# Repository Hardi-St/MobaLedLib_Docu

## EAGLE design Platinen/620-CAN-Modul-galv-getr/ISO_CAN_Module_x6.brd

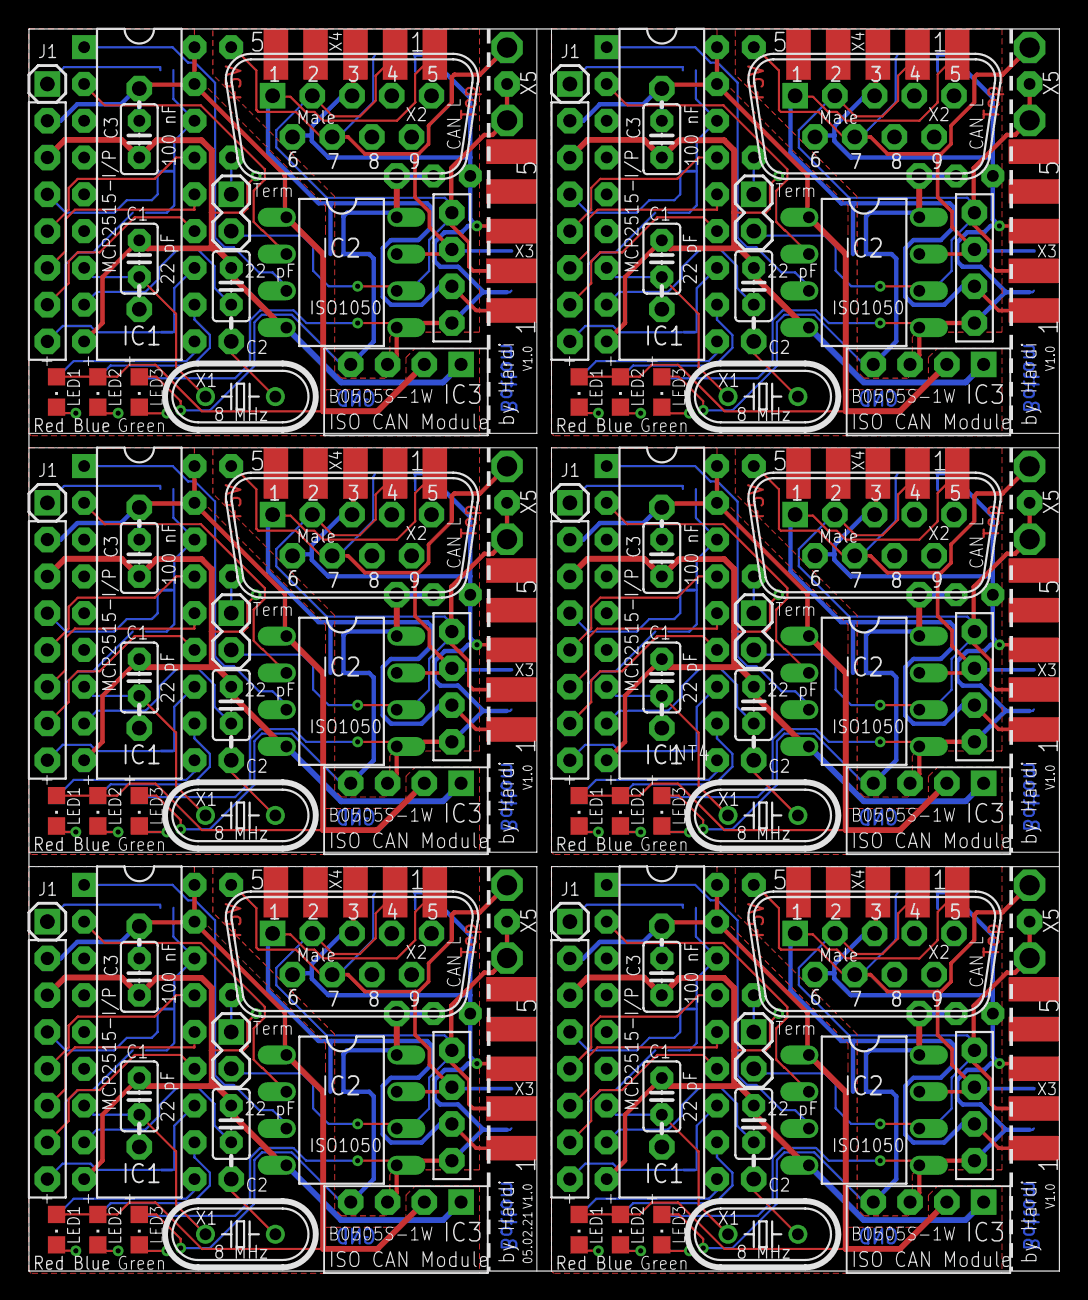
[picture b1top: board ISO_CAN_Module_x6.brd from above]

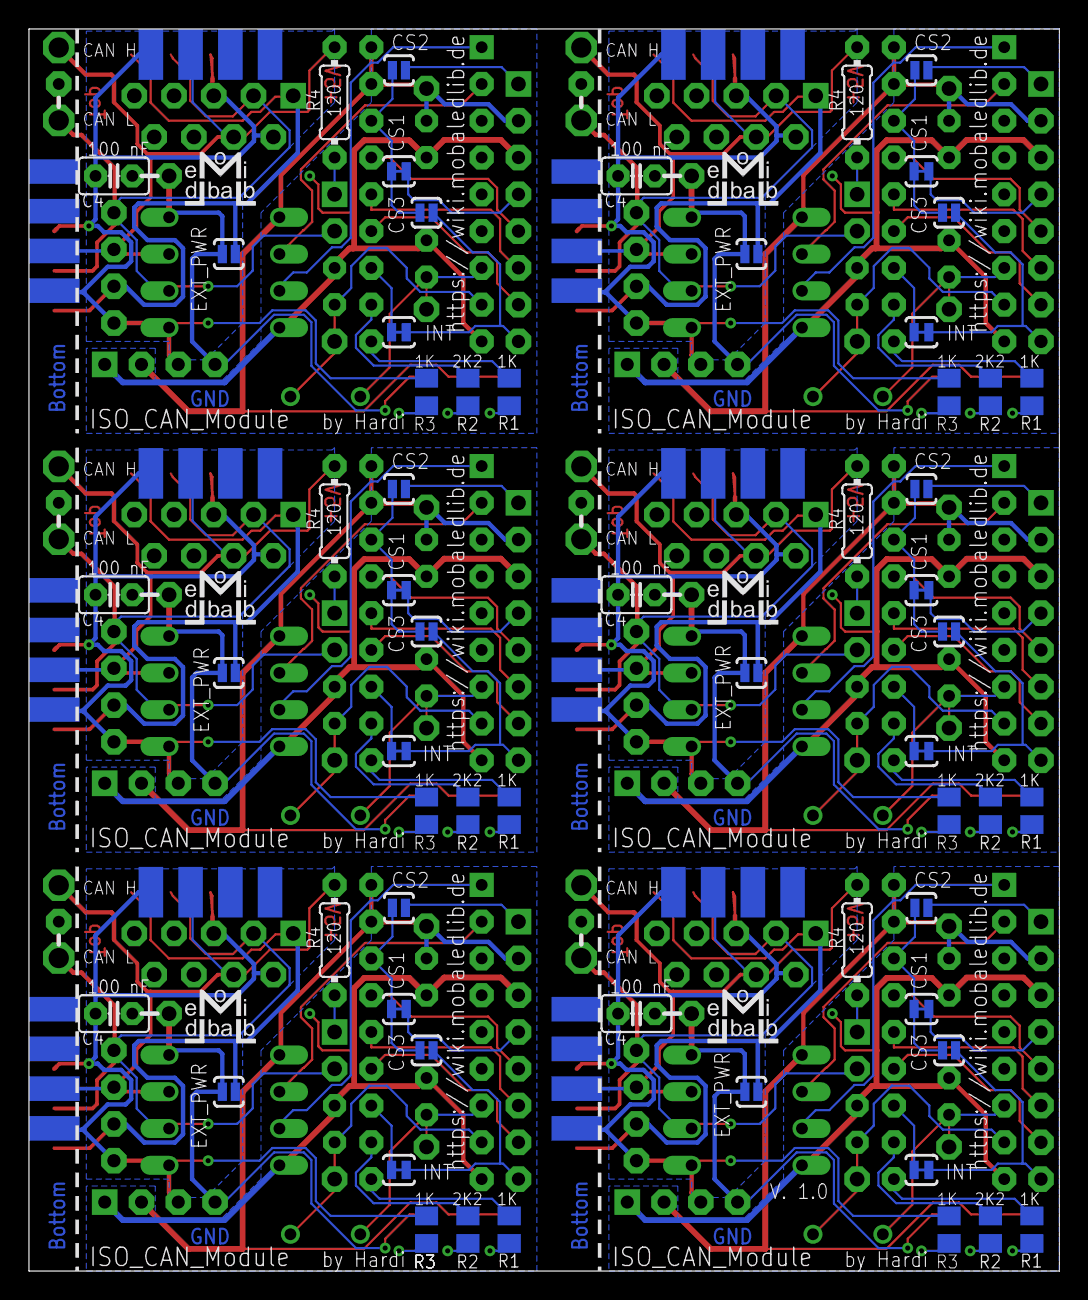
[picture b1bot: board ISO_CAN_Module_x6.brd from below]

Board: 2 copper layers, 71.2 x 85.8 mm, 186 parts (60 on the bottom side), 150 nets.

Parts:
C1, C2, C5, C6, C9, C10, C13, C14, C17, C18, C21, C22: 22 pF; C2.5-2
C3, C4, C7, C8, C11, C12, C15, C16, C19, C20, C23, C24: 100 nF; C2.5-2
CAN1, CAN2, CAN3, CAN4, CAN5, CAN6: MCP2515_ISO_CAN_PINS; MCP2515_ISO_CAN
CON1, CON2, CON3, CON4, CON5, CON8: Term; 1X02
CS1, CS5, CS8, CS11, CS14, CS17: SOLDERJUMPERTRACE; SJ_2S-TRACE
CS2, CS3, CS4, CS6, CS7, CS9, CS10, CS12, CS13, CS15, CS16, CS18: SOLDERJUMPERNO; SJ_2S-NO
EXT_PWR, EXT_PWR1, EXT_PWR2, EXT_PWR3, EXT_PWR4, EXT_PWR5: SOLDERJUMPERNO; SJ_2S-NO
IC1, IC5, IC8, IC11, IC14, IC17: MCP2515-I/P; DIL18
IC2, IC4, IC7, IC10, IC13, IC16: ISO1050; DIL08
IC3, IC6, IC9, IC12, IC15, IC18: B0505S-1W; DCDC-TEA_NME
INT, INT1, INT2, INT3, INT4, INT5: SOLDERJUMPERTRACE; SJ_2S-TRACE
J1, J6, J11, J16, J21, J26: 1X01
J2, J3, J4, J5, J7, J8, J9, J10, J12, J13, J14, J15, J17, J18, J19, J20, J22, J23, J24, J25, J27, J28, J29, J30: 1X01S
LED1, LED5, LED8, LED11, LED14, LED17: Red; CHIPLED_0805
LED2, LED4, LED7, LED10, LED13, LED16: Blue; CHIPLED_0805
LED3, LED6, LED9, LED12, LED15, LED18: Green; CHIPLED_0805
R1, R3, R6, R8, R10, R12, R14, R16, R18, R20, R22, R24: 1K; M0805
R2, R5, R9, R13, R17, R21: 2K2; M0805
R4, R7, R11, R15, R19, R23: 120; 0204/7
X1, X6, X11, X16, X21, X26: 8 MHz; HC49U-V
X2, X8, X13, X18, X23, X28: Male; M09VB
X3, X4, X7, X9, X12, X14, X17, X19, X22, X24, X27, X29: Male; M09D
X5, X10, X15, X20, X25, X30: AK500/2+M

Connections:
+5V: C3.1, CAN1.1, IC1.17, IC1.18, IC2.1, IC3.V_IN, J4.1, LED1.A, LED2.A
+5V1: C7.1, CAN2.1, IC4.1, IC5.17, IC5.18, IC6.V_IN, J9.1, LED4.A, LED5.A
+5V2: C11.1, CAN3.1, IC7.1, IC8.17, IC8.18, IC9.V_IN, J14.1, LED7.A, LED8.A
+5V3: C15.1, CAN4.1, IC10.1, IC11.17, IC11.18, IC12.V_IN, J19.1, LED10.A, LED11.A
+5V4: C19.1, CAN5.1, IC13.1, IC14.17, IC14.18, IC15.V_IN, J24.1, LED13.A, LED14.A
+5V5: C23.1, CAN6.1, IC16.1, IC17.17, IC17.18, IC18.V_IN, J29.1, LED16.A, LED17.A
CAN_H: CAN1.9, IC2.7, R4.2, X2.7, X3.7, X4.7, X5.2
CAN_H1: CAN2.9, IC4.7, R7.2, X7.7, X8.7, X9.7, X10.2
CAN_H2: CAN3.9, IC7.7, R11.2, X12.7, X13.7, X14.7, X15.2
CAN_H3: CAN4.9, IC10.7, R15.2, X17.7, X18.7, X19.7, X20.2
CAN_H4: CAN5.9, IC13.7, R19.2, X22.7, X23.7, X24.7, X25.2
CAN_H5: CAN6.9, IC16.7, R23.2, X27.7, X28.7, X29.7, X30.2
CAN_L: CAN1.8, CON8.2, IC2.6, X2.2, X3.2, X4.2, X5.1, X5.M
CAN_L1: CAN2.8, CON1.2, IC4.6, X7.2, X8.2, X9.2, X10.1, X10.M
CAN_L2: CAN3.8, CON2.2, IC7.6, X12.2, X13.2, X14.2, X15.1, X15.M
CAN_L3: CAN4.8, CON3.2, IC10.6, X17.2, X18.2, X19.2, X20.1, X20.M
CAN_L4: CAN5.8, CON4.2, IC13.6, X22.2, X23.2, X24.2, X25.1, X25.M
CAN_L5: CAN6.8, CON5.2, IC16.6, X27.2, X28.2, X29.2, X30.1, X30.M
CS: CS1.2, CS2.2, CS3.2, IC1.16
CS1: CS4.2, CS5.2, CS6.2, IC5.16
CS2: CS7.2, CS8.2, CS9.2, IC8.16
CS3: CS10.2, CS11.2, CS12.2, IC11.16
CS4: CS13.2, CS14.2, CS15.2, IC14.16
CS5: CS16.2, CS17.2, CS18.2, IC17.16
CS_CAN0: CAN1.3, CS1.1
CS_CAN1: CAN2.3, CS5.1
CS_CAN2: CAN3.3, CS8.1
CS_CAN3: CAN4.3, CS11.1
CS_CAN4: CAN5.3, CS14.1
CS_CAN5: CAN6.3, CS17.1
CS_INT: CAN1.7, CS3.1, INT.1
CS_INT1: CAN2.7, CS6.1, INT1.1
CS_INT2: CAN3.7, CS9.1, INT2.1
CS_INT3: CAN4.7, CS12.1, INT3.1
CS_INT4: CAN5.7, CS15.1, INT4.1
CS_INT5: CAN6.7, CS18.1, INT5.1
CS_J1: CS2.1, J1.1
CS_J2: CS4.1, J6.1
CS_J3: CS7.1, J11.1
CS_J4: CS10.1, J16.1
CS_J5: CS13.1, J21.1
CS_J6: CS16.1, J26.1
GND: C1.2, C2.2, C3.2, CAN1.2, IC1.9, IC2.4, IC3.G_IN
GND1: C5.2, C6.2, C7.2, CAN2.2, IC4.4, IC5.9, IC6.G_IN
GND2: C4.1, CAN1.11, IC2.5, IC3.G_OUT, R3.1, X2.3, X2.6, X3.3, X3.6, X4.3, X4.6
GND3: C8.1, CAN2.11, IC4.5, IC6.G_OUT, R8.1, X7.3, X7.6, X8.3, X8.6, X9.3, X9.6
GND4: C9.2, C10.2, C11.2, CAN3.2, IC7.4, IC8.9, IC9.G_IN
GND5: C12.1, CAN3.11, IC7.5, IC9.G_OUT, R12.1, X12.3, X12.6, X13.3, X13.6, X14.3, X14.6
GND6: C13.2, C14.2, C15.2, CAN4.2, IC10.4, IC11.9, IC12.G_IN
GND7: C16.1, CAN4.11, IC10.5, IC12.G_OUT, R16.1, X17.3, X17.6, X18.3, X18.6, X19.3, X19.6
GND8: C17.2, C18.2, C19.2, CAN5.2, IC13.4, IC14.9, IC15.G_IN
GND9: C20.1, CAN5.11, IC13.5, IC15.G_OUT, R20.1, X22.3, X22.6, X23.3, X23.6, X24.3, X24.6
GND10: C21.2, C22.2, C23.2, CAN6.2, IC16.4, IC17.9, IC18.G_IN
GND11: C24.1, CAN6.11, IC16.5, IC18.G_OUT, R24.1, X27.3, X27.6, X28.3, X28.6, X29.3, X29.6
INT0: IC1.12, INT.2
INT1: IC5.12, INT1.2
INT2: IC8.12, INT2.2
INT3: IC11.12, INT3.2
INT4: IC14.12, INT4.2
INT5: IC17.12, INT5.2
LED1: LED1.C, R1.1
LED2: LED2.C, R2.1
LED3: LED3.C, R3.2
LED4: LED4.C, R5.1
LED5: LED5.C, R6.1
LED6: LED6.C, R8.2
LED7: LED7.C, R9.1
LED8: LED8.C, R10.1
LED9: LED9.C, R12.2
LED10: LED10.C, R13.1
LED11: LED11.C, R14.1
LED12: LED12.C, R16.2
LED13: LED13.C, R17.1
LED14: LED14.C, R18.1
LED15: LED15.C, R20.2
LED16: LED16.C, R21.1
LED17: LED17.C, R22.1
LED18: LED18.C, R24.2
unnamed: IC5.11, R5.2
unnamed: IC5.10, R6.2
unnamed: IC8.11, R9.2
unnamed: IC8.10, R10.2
unnamed: IC11.11, R13.2
unnamed: IC11.10, R14.2
unnamed: IC14.11, R17.2
unnamed: IC14.10, R18.2
unnamed: IC1.11, R2.2
unnamed: IC17.11, R21.2
unnamed: IC17.10, R22.2
unnamed: IC1.10, R1.2
OSC1: C2.1, IC1.8, J3.1, X1.2
OSC2: C1.1, IC1.7, J2.1, X1.1
OSC3: C5.1, IC5.7, J7.1, X6.1
OSC4: C6.1, IC5.8, J8.1, X6.2
OSC5: C9.1, IC8.7, J12.1, X11.1
OSC6: C10.1, IC8.8, J13.1, X11.2
OSC7: C13.1, IC11.7, J17.1, X16.1
OSC8: C14.1, IC11.8, J18.1, X16.2
OSC9: C17.1, IC14.7, J22.1, X21.1
OSC10: C18.1, IC14.8, J23.1, X21.2
OSC11: C21.1, IC17.7, J27.1, X26.1
OSC12: C22.1, IC17.8, J28.1, X26.2
RXCAN: IC1.2, IC2.2
RXCAN1: IC4.2, IC5.2
RXCAN2: IC7.2, IC8.2
RXCAN3: IC10.2, IC11.2
RXCAN4: IC13.2, IC14.2
RXCAN5: IC16.2, IC17.2
SCK: CAN1.6, IC1.13
SCK1: CAN2.6, IC5.13
SCK2: CAN3.6, IC8.13
SCK3: CAN4.6, IC11.13
SCK4: CAN5.6, IC14.13
SCK5: CAN6.6, IC17.13
SI: CAN1.5, IC1.14
SI1: CAN2.5, IC5.14
SI2: CAN3.5, IC8.14
SI3: CAN4.5, IC11.14
SI4: CAN5.5, IC14.14
SI5: CAN6.5, IC17.14
SO: CAN1.4, IC1.15
SO1: CAN2.4, IC5.15
SO2: CAN3.4, IC8.15
SO3: CAN4.4, IC11.15
SO4: CAN5.4, IC14.15
SO5: CAN6.4, IC17.15
TERM: CON8.1, R4.1
TERM1: CON1.1, R7.1
TERM2: CON2.1, R11.1
TERM3: CON3.1, R15.1
TERM4: CON4.1, R19.1
TERM5: CON5.1, R23.1
TXCAN: IC1.1, IC2.3
TXCAN1: IC4.3, IC5.1
TXCAN2: IC7.3, IC8.1
TXCAN3: IC10.3, IC11.1
TXCAN4: IC13.3, IC14.1
TXCAN5: IC16.3, IC17.1
VCC1: C8.2, EXT_PWR1.1, IC4.8, IC6.V_OUT, J10.1, LED6.A
VCC2: C4.2, EXT_PWR.1, IC2.8, IC3.V_OUT, J5.1, LED3.A
VCC2_EXT: CAN1.10, EXT_PWR.2, X2.1, X3.1, X4.1
VCC2_EXT1: CAN2.10, EXT_PWR1.2, X7.1, X8.1, X9.1
VCC2_EXT2: CAN3.10, EXT_PWR2.2, X12.1, X13.1, X14.1
VCC2_EXT3: CAN4.10, EXT_PWR3.2, X17.1, X18.1, X19.1
VCC2_EXT4: CAN5.10, EXT_PWR4.2, X22.1, X23.1, X24.1
VCC2_EXT5: CAN6.10, EXT_PWR5.2, X27.1, X28.1, X29.1
VCC3: C12.2, EXT_PWR2.1, IC7.8, IC9.V_OUT, J15.1, LED9.A
VCC4: C16.2, EXT_PWR3.1, IC10.8, IC12.V_OUT, J20.1, LED12.A
VCC5: C20.2, EXT_PWR4.1, IC13.8, IC15.V_OUT, J25.1, LED15.A
VCC6: C24.2, EXT_PWR5.1, IC16.8, IC18.V_OUT, J30.1, LED18.A

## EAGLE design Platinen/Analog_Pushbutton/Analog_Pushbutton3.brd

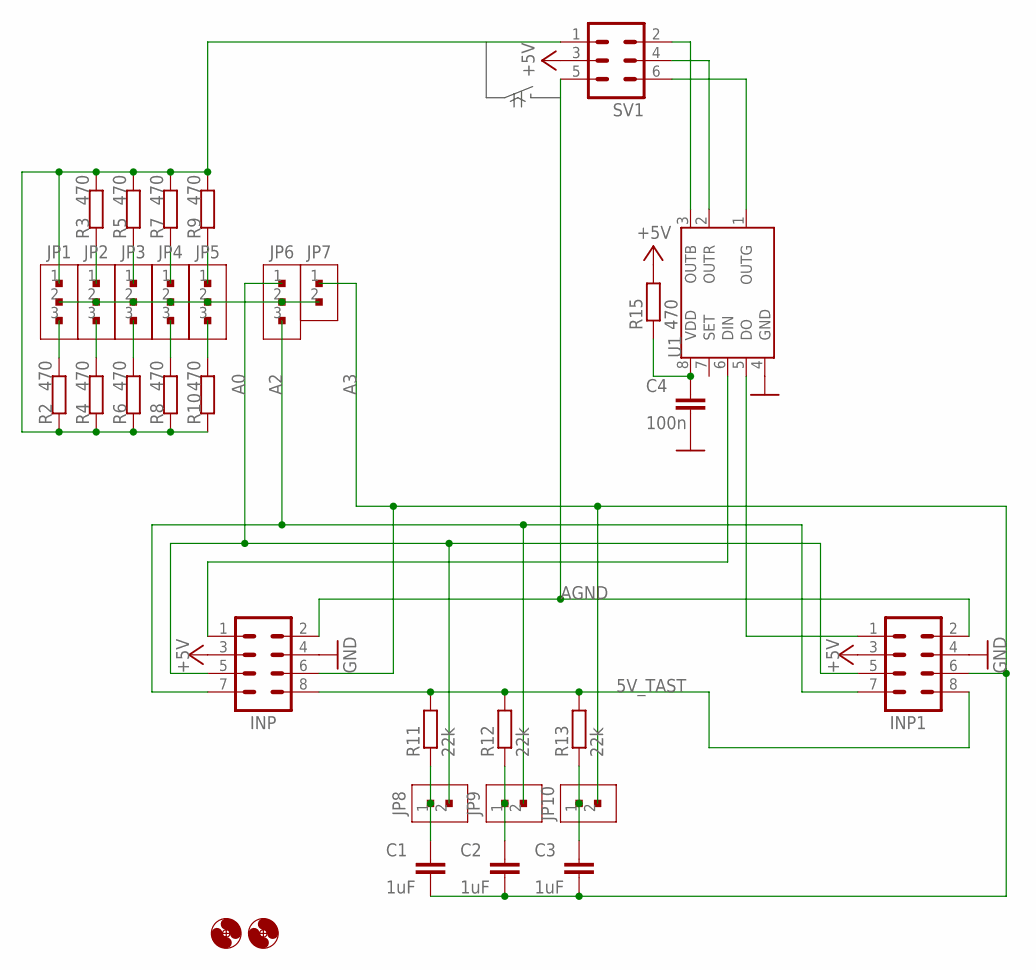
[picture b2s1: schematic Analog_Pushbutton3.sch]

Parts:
C1, C2, C3: 1uF; C0603
C4: 100n; C0603
H1, H2: MOUNT-HOLE3.0; 3,0
INP, INP1: CON-HARTING-ML_ML08
JP1, JP2, JP3, JP4, JP5, JP6: PINHD-1X3CB; 1X03-CLEANBIG
JP7, JP8, JP9, JP10: PINHD-1X2; 1X02
R2, R3, R4, R5, R6, R7, R8, R9, R10, R15: 470; R0603
R11, R12, R13: 22k; R0603
SV1: CON-HARTING-ML_ML6
U1: S3PO_MODUL_WS2811_SOUND_MP3-TF-16P_WS2811_AND_ATT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; SOP8

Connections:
5V_TAST: INP.8, INP1.8, R11.2, R12.2, R13.2
+5V: INP.3, INP1.3, R15.2, SV1.3
A0: INP.5, INP1.5, JP6.1, JP8.2
A2: INP.7, INP1.7, JP6.3, JP9.2
A3: C1.2, C2.2, C3.2, INP.6, INP1.6, JP7.1, JP10.2
AGND: INP.2, INP1.2, SV1.5
GND: C4.2, INP.4, INP1.4, U1.4 (GND)
unnamed: SV1.4, U1.2 (OUTR)
unnamed: SV1.6, U1.1 (OUTG)
unnamed: SV1.2, U1.3 (OUTB)
unnamed: INP.1, U1.6 (DIN)
unnamed: INP1.1, U1.5 (DO)
unnamed: C1.1, JP8.1, R11.1
unnamed: JP1.3, R2.2
unnamed: JP1.1, R2.1, R3.2, R4.1, R5.2, R6.1, R7.2, R8.1, R9.2, R10.1, SV1.1
unnamed: JP2.3, R4.2
unnamed: JP2.1, R3.1
unnamed: JP3.3, R6.2
unnamed: JP3.1, R5.1
unnamed: JP4.3, R8.2
unnamed: JP4.1, R7.1
unnamed: JP5.3, R10.2
unnamed: JP5.1, R9.1
unnamed: C2.1, JP9.1, R12.1
unnamed: C3.1, JP10.1, R13.1
unnamed: JP1.2, JP2.2, JP3.2, JP4.2, JP5.2, JP6.2, JP7.2
unnamed: C4.1, R15.1, U1.8 (VDD)

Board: 2 copper layers, 33 parts (0 on the bottom side), 27 nets, no tracks yet.

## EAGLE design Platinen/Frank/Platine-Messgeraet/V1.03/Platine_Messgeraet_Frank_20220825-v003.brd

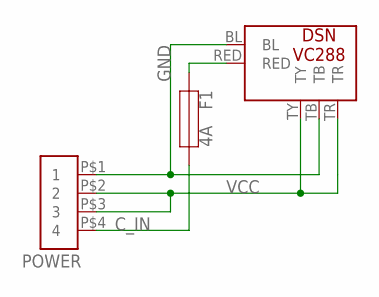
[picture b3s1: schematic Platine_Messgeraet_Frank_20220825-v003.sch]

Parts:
F1: 4A; FUSE_5X20-L
POWER: CB-SCREW-4P0°; CTB932VD-4
U$1: DSN-VC288

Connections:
C_IN: F1.1, POWER.P$4 (4)
GND: POWER.P$1 (1), U$1.BL, U$1.TB
unnamed: F1.2, U$1.RED
VCC: POWER.P$2 (2), POWER.P$3 (3), U$1.TR, U$1.TY

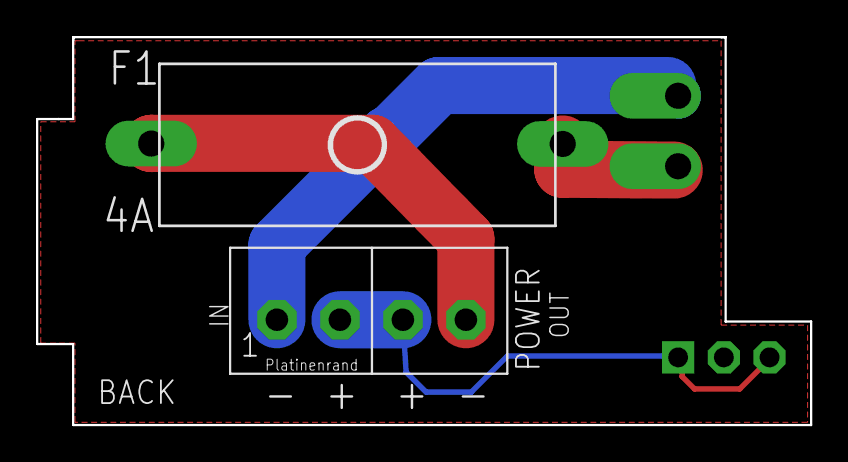
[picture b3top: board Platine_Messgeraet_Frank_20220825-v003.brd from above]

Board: 2 copper layers, 43.0 x 21.6 mm, 3 parts (0 on the bottom side), 4 nets.

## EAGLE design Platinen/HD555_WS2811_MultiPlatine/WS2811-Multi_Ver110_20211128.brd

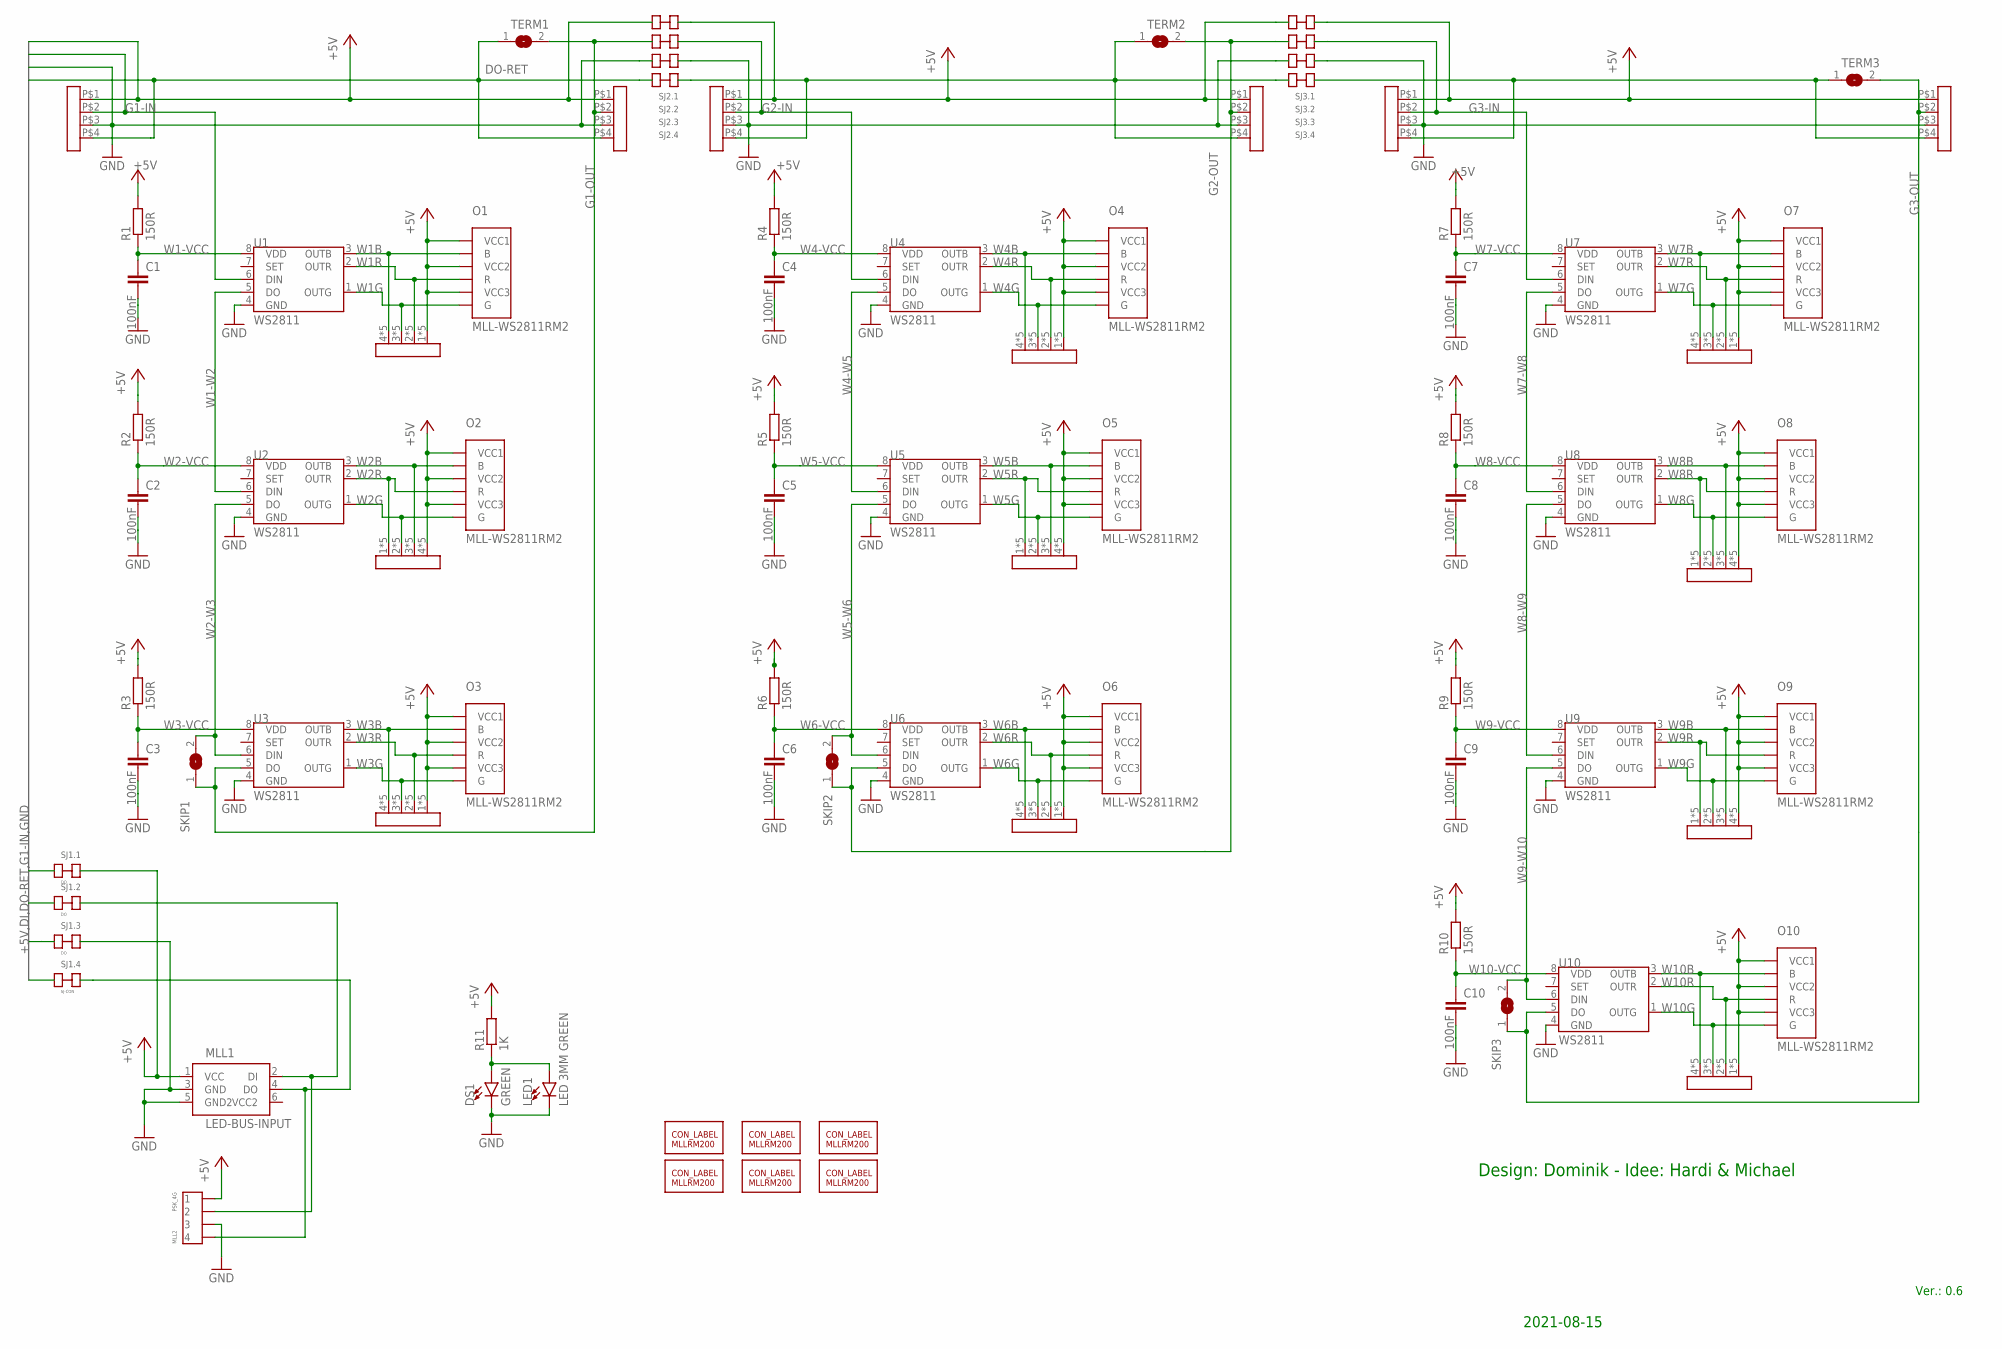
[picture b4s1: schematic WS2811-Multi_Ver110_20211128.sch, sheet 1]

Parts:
C1, C2, C3, C4, C5, C6, C7, C8, C9, C10: 100nF; C1206
DS1: GREEN; LED-1206
LED1: LED 3MM GREEN; LED_3MM
M1_IN, M1_OUT, M2_IN, M2_OUT, M3_IN, M3_OUT: 4XRM254
MLL1: LED-BUS-INPUT; IDC6
MLL2: PSK_4G; PSSG4
O1, O2, O3, O4, O5, O6, O7, O8, O9, O10: MLL-WS2811RM2; MLL-WS2811-RM2
R1, R2, R3, R4, R5, R6, R7, R8, R9, R10: 150R; R1206
R11: 1K; R1206
SJ1.1, SJ1.2, SJ1.3: DO; SJ-CON
SJ1.4, SJ2.1, SJ2.2, SJ2.3, SJ2.4, SJ3.1, SJ3.2, SJ3.3, SJ3.4: SJ-CON
SKIP1, SKIP2, SKIP3: SJ
TERM1, TERM2, TERM3: SJ
U1, U2, U3, U4, U5, U6, U7, U8, U9, U10: WS2811; SOP8
U$1, U$3, U$4: CON-LABEL_MLLRM200_2RGB_M; CON-LABEL_MLLRM200_RGB_M
U$2, U$6: CON-LABEL_MLLRM200
U$5: CON-LABEL_MLLRM200_2RGB; CON-LABEL_MLLRM200_RGB
U$7, U$8, U$9, U$14, U$15, U$16, U$17, U$18, U$19, U$20: 4XRM200LONG-NOH_DOUBLE; 4XRM200LONG_NOH_DOUBLE

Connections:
+5V: M1_IN.P$1, M1_OUT.P$1, M2_IN.P$1, M2_OUT.P$1, M3_IN.P$1, M3_OUT.P$1, MLL1.1 (VCC), MLL2.P$1 (1), O1.VCC1, O1.VCC2, O1.VCC3, O2.VCC1, O2.VCC2, O2.VCC3, O3.VCC1, O3.VCC2, O3.VCC3, O4.VCC1, O4.VCC2, O4.VCC3, O5.VCC1, O5.VCC2, O5.VCC3, O6.VCC1, O6.VCC2, O6.VCC3, O7.VCC1, O7.VCC2, O7.VCC3, O8.VCC1, O8.VCC2, O8.VCC3, O9.VCC1, O9.VCC2, O9.VCC3, O10.VCC1, O10.VCC2, O10.VCC3, R1.2, R2.2, R3.2, R4.2, R5.2, R6.2, R7.2, R8.2, R9.2, R10.2, R11.2, SJ1.1.P$1, SJ1.1.P$2, SJ2.1.P$1, SJ2.1.P$2, SJ3.1.P$1, SJ3.1.P$2, U$7.1, U$7.1B, U$7.11, U$7.12, U$7.13, U$8.4, U$8.4B, U$8.41, U$8.42, U$8.43, U$9.1, U$9.1B, U$9.11, U$9.12, U$9.13, U$14.1, U$14.1B, U$14.11, U$14.12, U$14.13, U$15.4, U$15.4B, U$15.41, U$15.42, U$15.43, U$16.1, U$16.1B, U$16.11, U$16.12, U$16.13, U$17.1, U$17.1B, U$17.11, U$17.12, U$17.13, U$18.4, U$18.4B, U$18.41, U$18.42, U$18.43, U$19.4, U$19.4B, U$19.41, U$19.42, U$19.43, U$20.1, U$20.1B, U$20.11, U$20.12, U$20.13
DI: MLL1.2 (DI), MLL2.P$2 (2), SJ1.2.P$2
DO: MLL1.4 (DO), MLL2.P$4 (4), SJ1.4.P$2
DO-RET: M1_IN.P$4, M1_OUT.P$4, SJ1.4.P$1, SJ2.4.P$1, TERM1.1
G1-IN: M1_IN.P$2, SJ1.2.P$1, U1.6 (DIN)
G1-OUT: M1_OUT.P$2, SJ2.2.P$1, SKIP1.1, TERM1.2, U3.5 (DO)
G2-IN: M2_IN.P$2, SJ2.2.P$2, U4.6 (DIN)
G2-OUT: M2_OUT.P$2, SJ3.2.P$1, SKIP2.1, TERM2.2, U6.5 (DO)
G2-RET: M2_IN.P$4, M2_OUT.P$4, SJ2.4.P$2, SJ3.4.P$1, TERM2.1
G3-IN: M3_IN.P$2, SJ3.2.P$2, U7.6 (DIN)
G3-OUT: M3_OUT.P$2, SKIP3.1, TERM3.2, U10.5 (DO)
G3-RET: M3_IN.P$4, M3_OUT.P$4, SJ3.4.P$2, TERM3.1
GND: C1.2, C2.2, C3.2, C4.2, C5.2, C6.2, C7.2, C8.2, C9.2, C10.2, DS1.C, LED1.K (C), M1_IN.P$3, M1_OUT.P$3, M2_IN.P$3, M2_OUT.P$3, M3_IN.P$3, M3_OUT.P$3, MLL1.3 (GND), MLL1.5 (GND2), MLL2.P$3 (3), SJ1.3.P$1, SJ1.3.P$2, SJ2.3.P$1, SJ2.3.P$2, SJ3.3.P$1, SJ3.3.P$2, U1.4 (GND), U2.4 (GND), U3.4 (GND), U4.4 (GND), U5.4 (GND), U6.4 (GND), U7.4 (GND), U8.4 (GND), U9.4 (GND), U10.4 (GND)
LED1: DS1.A, LED1.A, R11.1
VCC2: MLL1.6 (VCC2)
W1-VCC: C1.1, R1.1, U1.8 (VDD)
W1-W2: U1.5 (DO), U2.6 (DIN)
W1B: O1.B, U1.3 (OUTB), U$9.4, U$9.4B, U$9.41, U$9.42, U$9.43
W1G: O1.G, U1.1 (OUTG), U$9.3, U$9.3B, U$9.31, U$9.32, U$9.33
W1R: O1.R, U1.2 (OUTR), U$9.2, U$9.2B, U$9.21, U$9.22, U$9.23
W2-VCC: C2.1, R2.1, U2.8 (VDD)
W2-W3: SKIP1.2, U2.5 (DO), U3.6 (DIN)
W2B: O2.B, U2.3 (OUTB), U$8.3, U$8.3B, U$8.31, U$8.32, U$8.33
W2G: O2.G, U2.1 (OUTG), U$8.2, U$8.2B, U$8.21, U$8.22, U$8.23
W2R: O2.R, U2.2 (OUTR), U$8.1, U$8.1B, U$8.11, U$8.12, U$8.13
W3-VCC: C3.1, R3.1, U3.8 (VDD)
W3B: O3.B, U3.3 (OUTB), U$7.4, U$7.4B, U$7.41, U$7.42, U$7.43
W3G: O3.G, U3.1 (OUTG), U$7.3, U$7.3B, U$7.31, U$7.32, U$7.33
W3R: O3.R, U3.2 (OUTR), U$7.2, U$7.2B, U$7.21, U$7.22, U$7.23
W4-VCC: C4.1, R4.1, U4.8 (VDD)
W4-W5: U4.5 (DO), U5.6 (DIN)
W4B: O4.B, U4.3 (OUTB), U$14.4, U$14.4B, U$14.41, U$14.42, U$14.43
W4G: O4.G, U4.1 (OUTG), U$14.3, U$14.3B, U$14.31, U$14.32, U$14.33
W4R: O4.R, U4.2 (OUTR), U$14.2, U$14.2B, U$14.21, U$14.22, U$14.23
W5-VCC: C5.1, R5.1, U5.8 (VDD)
W5-W6: SKIP2.2, U5.5 (DO), U6.6 (DIN)
W5B: O5.B, U5.3 (OUTB), U$15.3, U$15.3B, U$15.31, U$15.32, U$15.33
W5G: O5.G, U5.1 (OUTG), U$15.2, U$15.2B, U$15.21, U$15.22, U$15.23
W5R: O5.R, U5.2 (OUTR), U$15.1, U$15.1B, U$15.11, U$15.12, U$15.13
W6-VCC: C6.1, R6.1, U6.8 (VDD)
W6B: O6.B, U6.3 (OUTB), U$16.4, U$16.4B, U$16.41, U$16.42, U$16.43
W6G: O6.G, U6.1 (OUTG), U$16.3, U$16.3B, U$16.31, U$16.32, U$16.33
W6R: O6.R, U6.2 (OUTR), U$16.2, U$16.2B, U$16.21, U$16.22, U$16.23
W7-VCC: C7.1, R7.1, U7.8 (VDD)
W7-W8: U7.5 (DO), U8.6 (DIN)
W7B: O7.B, U7.3 (OUTB), U$17.4, U$17.4B, U$17.41, U$17.42, U$17.43
W7G: O7.G, U7.1 (OUTG), U$17.3, U$17.3B, U$17.31, U$17.32, U$17.33
W7R: O7.R, U7.2 (OUTR), U$17.2, U$17.2B, U$17.21, U$17.22, U$17.23
W8-VCC: C8.1, R8.1, U8.8 (VDD)
W8-W9: U8.5 (DO), U9.6 (DIN)
W8B: O8.B, U8.3 (OUTB), U$18.3, U$18.3B, U$18.31, U$18.32, U$18.33
W8G: O8.G, U8.1 (OUTG), U$18.2, U$18.2B, U$18.21, U$18.22, U$18.23
W8R: O8.R, U8.2 (OUTR), U$18.1, U$18.1B, U$18.11, U$18.12, U$18.13
W9-VCC: C9.1, R9.1, U9.8 (VDD)
W9-W10: SKIP3.2, U9.5 (DO), U10.6 (DIN)
W9B: O9.B, U9.3 (OUTB), U$19.3, U$19.3B, U$19.31, U$19.32, U$19.33
W9G: O9.G, U9.1 (OUTG), U$19.2, U$19.2B, U$19.21, U$19.22, U$19.23
W9R: O9.R, U9.2 (OUTR), U$19.1, U$19.1B, U$19.11, U$19.12, U$19.13
W10-VCC: C10.1, R10.1, U10.8 (VDD)
W10B: O10.B, U10.3 (OUTB), U$20.4, U$20.4B, U$20.41, U$20.42, U$20.43
W10G: O10.G, U10.1 (OUTG), U$20.3, U$20.3B, U$20.31, U$20.32, U$20.33
W10R: O10.R, U10.2 (OUTR), U$20.2, U$20.2B, U$20.21, U$20.22, U$20.23

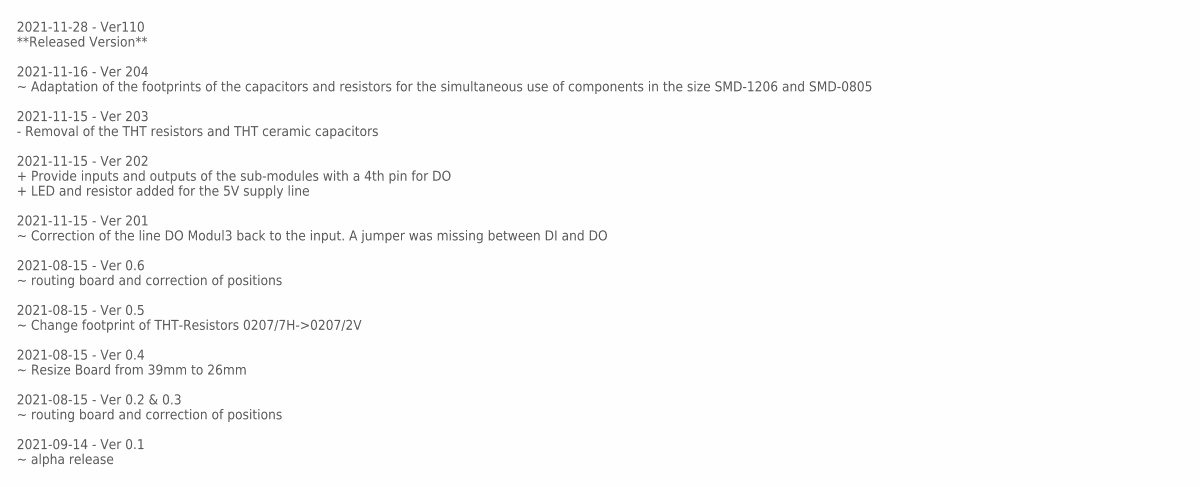
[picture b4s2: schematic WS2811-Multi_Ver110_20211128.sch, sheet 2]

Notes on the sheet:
2021-11-28 - Ver110 **Released Version** 2021-11-16 - Ver 204 ~ Adaptation of the footprints of the capacitors and resistors for the simultaneous use of components in the size SMD-1206 and SMD-0805 2021-11-15 - Ver 203 - Removal of the THT resistors and THT ceramic capacitors 2021-11-15 - Ver 202 +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

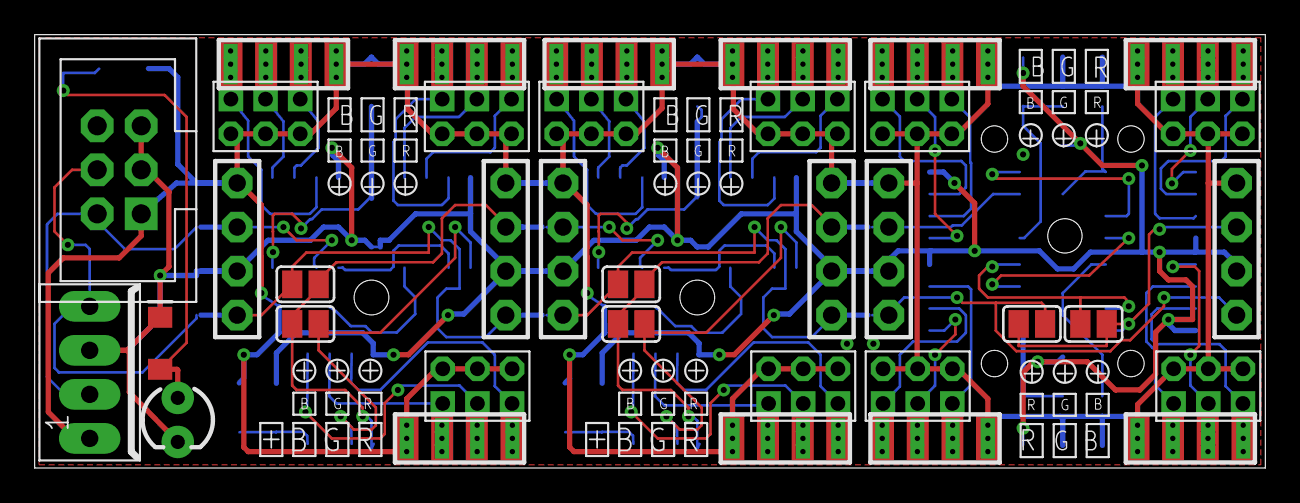
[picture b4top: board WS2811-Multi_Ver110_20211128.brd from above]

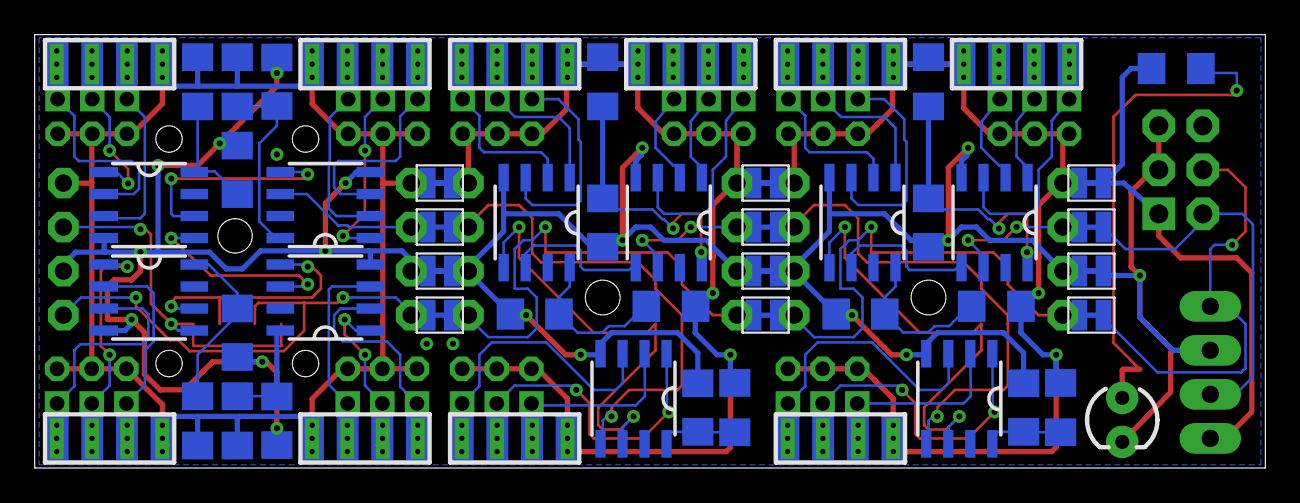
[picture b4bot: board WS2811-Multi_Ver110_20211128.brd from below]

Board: 2 copper layers, 71.0 x 25.0 mm, 85 parts (44 on the bottom side), 61 nets.

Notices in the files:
parts and their libraries:
SparkFun-Retired: Licensing:Creative Commons ShareAlike 4.0 International - https://creativecommons.org/licenses/by-sa/4.0
